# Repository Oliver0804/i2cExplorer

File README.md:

# i2cExplorer

## Introduction

https://www.youtube.com/watch?v=PAolOif3dD0&ab_channel=BashCat

i2cExplorer is a powerful tool designed for exploring I2C devices on the bus using the RP2040 as the MCU within the Arduino framework. It allows users to interact with I2C devices via a serial interface, providing capabilities for scanning, reading, and writing I2C registers.

『I2C Explorer』是一個非常實用的工具，特別適合於解決在使用I2C通訊協議時可能遇到的一些常見問題和場景。以下是幾個典型的使用場景，以及I2C Explorer如何幫助解決這些問題：
1. 不知道I2C裝置的地址：在開發I2C應用時，常常需要知道連接到I2C總線的裝置地址。如果文檔不清楚或者你正在使用未標記的硬件，I2C Explorer的掃描功能（scana命令）可以掃描總線上的所有裝置，幫助你快速找到每個裝置的地址。
2. 混淆了SDA和SCL線：有時可能會不小心將SDA（數據線）和SCL（時鐘線）接反。I2C Explorer提供了一個方便的命令（s命令），可以在不重新布線的情況下軟件層面上交換這兩條線，從而糾正連接錯誤。
3. 探索特定I2C裝置的寄存器：當你需要了解某個特定I2C裝置的內部寄存器結構時，I2C Explorer的寄存器掃描功能（scanr命令）可以讀取並顯示連接到指定地址的I2C裝置的所有寄存器信息。
4. 讀取或寫入I2C裝置的寄存器：在開發和調試階段，直接從串口讀取或寫入I2C裝置的寄存器是非常有用的。I2C Explorer通過提供讀取（r命令）和寫入（w命令）命令，使這一過程變得簡單快捷。

I2C Explorer is an extremely practical tool, particularly suited for addressing common problems and scenarios encountered when using the I2C communication protocol. Below are several typical use cases, and how the I2C Explorer helps in resolving these issues:
1. Unknown I2C Device Address: During the development of I2C applications, it's often necessary to know the addresses of devices connected to the I2C bus. If documentation is unclear or you are working with unmarked hardware, the scanning feature (scana command) of I2C Explorer can scan all devices on the bus, helping you quickly find the address of each device.
2. Confusion between SDA and SCL Lines: Sometimes, you might accidentally reverse the SDA (data line) and SCL (clock line). I2C Explorer offers a convenient command (s command) that swaps these two lines at the software level without the need for rewiring, thereby correcting the connection error.
3. Exploring the Registers of a Specific I2C Device: When you need to understand the internal register structure of a particular I2C device, the register scanning feature (scanr command) of I2C Explorer can read and display all the register information of the device connected to a specified address.
4. Reading or Writing to I2C Device Registers: During the development and debugging phases, directly reading from or writing to the registers of an I2C device through the serial port is very useful. I2C Explorer simplifies this process by providing commands for reading (r command) and writing (w command).

## Hardware Setup

Connect any I2C device to your RP2040, using the following pins:
- SDA (Serial Data Line): Connect to GP0 on the Pico.
- SCL (Serial Clock Line): Connect to GP1 on the Pico.
Ensure that your I2C devices are compatible with the RP2040's voltage levels and properly powered.

## Features
- I2C Bus Scanning: Detect all I2C devices connected to the RP2040.
- Read I2C Registers: Read values from specified registers of the connected I2C devices.
- Write I2C Registers: Write data to specified registers of the connected I2C devices.
- Monitor I2C Registers: Continuously read and print values from a specific register at regular intervals.
- Serial Interface: Communicate with the RP2040 and I2C devices through a serial connection.
- Swap I2C bus ( SDA <-> SCL )

## Usage
### Command List
Execute the following commands through your serial terminal:

```
- `scana`: Scan all I2C devices on the bus.
- `scanr [address]`: Scan registers at the specified I2C address.
- `c [address]`: Connect to an I2C device at the given address.
- `r [register]`: Read from a register on the connected I2C device.
- `w [register] [data]`: Write data to a register on the connected I2C device.
- `m [register] [interval]`: Monitor a register at the specified interval (in milliseconds).
- `s` - Swap SDA and SCL pins if connected incorrectly
- `exit`: Disconnect from the current I2C device.
- `help`: Display available commands based on the connection status.
```
#### scana

#### c 0x68 and r 0x75

## Monitoring Interval
For the m command, the interval is optional (default is 500ms). The maximum allowed interval is 3000ms.

## Example

```
> scana
> c 0x68
> r 0x1
> w 0x1 0xFF
> m 0x1 1000
> exit
```
## PCB HW(Kicad 7)

## Note
Ensure your RP2040 and I2C devices are correctly connected and configured.
This tool is intended for exploration and debugging purposes.

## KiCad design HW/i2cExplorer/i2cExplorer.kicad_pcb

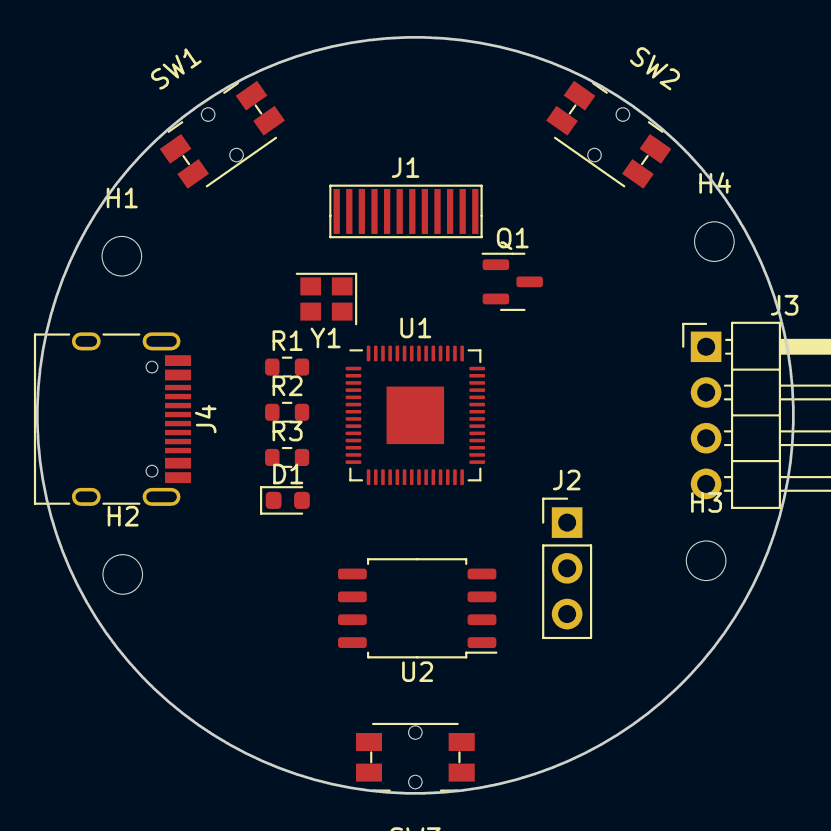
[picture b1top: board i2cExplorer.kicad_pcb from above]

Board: 2 copper layers, 42.0 x 42.0 mm, 19 parts (0 on the bottom side), 4 nets, no tracks yet.

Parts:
D1: LED; LED_0603_1608Metric
H1, H2, H3, H4: MountingHole; MountingHole_2.2mm_M2
J1: GC9A01; GC9A01_Extended_FPC
J2: SWDIO; PinHeader_1x03_P2.54mm_Vertical
J3: I2CTest; PinHeader_1x04_P2.54mm_Horizontal
J4: USB_C_Receptacle; USB_C_Receptacle_HRO_TYPE-C-31-M-12
Q1: S8050; SOT-23
R1, R2, R3: R; R_0603_1608Metric
SW1, SW2, SW3: SW_Push; Panasonic_EVQPUM_EVQPUD
U1: RP2040; QFN-56-1EP_7x7mm_P0.4mm_EP3.2x3.2mm
U2: W5Q16JVSSIQ; SOIC-8_5.23x5.23mm_P1.27mm
Y1: Crystal; Crystal_SMD_2520-4Pin_2.5x2.0mm

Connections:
unnamed: J4.A1 (GND), J4.A12 (GND), J4.B1 (GND), J4.B12 (GND)
unnamed: J4.A4 (VBUS), J4.A9 (VBUS), J4.B4 (VBUS), J4.B9 (VBUS)
unnamed: U1.23 (DVDD), U1.50 (DVDD)
unnamed: U1.1 (IOVDD), U1.10 (IOVDD), U1.22 (IOVDD), U1.33 (IOVDD), U1.42 (IOVDD), U1.49 (IOVDD)

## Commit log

2024-01-23 Create LICENSE
2024-01-23 add pic
2024-01-23 add hw setup
2024-01-24 add onboard led
2024-01-24 add oled
2024-01-24 add pico json
2024-01-24 add pico config pic
2024-01-24 更新第一階段
2024-01-25 add GC9A01
2024-01-25 add led pwm
2024-01-25 整理代碼
2024-01-25 update rotatePoint
2024-01-26 use soft i2c
2024-01-26 更新i2cScan使用軟體i2c
2024-01-26 添加i2c顯示狀態
2024-01-26 add pic swap
2024-01-26 update logo
2024-01-26 remove
2024-01-26 update pic
2024-01-26 udpate
2024-01-26 add kicad
2024-01-26 update sch
